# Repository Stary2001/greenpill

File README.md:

Greenpill
===
*Breadboard-able SAMD51 development board*

Inspired by the popular low-cost "Bluepill" and "Blackpill" STM32 boards, Greenpill aims to maintain some compatibility with those designs while adding features from the SAMD5x platform. Greenpill is designed to be used with [CircuitPython], although a SAMD51 port of Arduino could also be used.

## Features
 - SAMD51J20A-M microcontroller
   - Arm Cortex-M4 @ 120 MHz
   - 8 USB endpoints &ndash; enough for CDC & MSC (for CircuitPython), and some extras (eg. AUDIO)
 - Reversible USB Type-C connector supporting USB 2.0 data rates
 - On-board user LED and button
 - External 32.768 kHz crystal oscillator for RTC + clock source.
 - Up to 13 PWM-capable pins usable **simultaneously**
 - SPI flash footprint on underside - no pin conflicts with broken out pins (uses **SERCOM2**).

## Flashing CircuitPython
1. **TODO: add UF2 bootloader instructions**
2. [Build CircuitPython][BuildCPy] from [the fork][CPyFork]. Use the `atsamd` port and `BOARD=greenpill`.
3. Enter the UF2 bootloader by double-tapping the RESET button on Greenpill
4. You should now have a removable storage device called `CPYBOOT`. Copy `PATHTOUF2` to the root directory of this device. Once it has finished copying, `CPYBOOT` will disappear and `GREENPILL` will appear. You have now installed CircuitPython.

## Pin assignment
Pins are numbered **counter-clockwise** starting at the top-left pin (to the left of the USB-C connector).

| Greenpill Pin | GPIO name  | Available SERCOMs*               | Available PWM timers*                 | Comment                        |
|---------------|------------|----------------------------------|---------------------------------------|--------------------------------|
| User LED      | PB09       | -                                | TC4/WO[1]                             |                                |
| User Button   | PB06       | -                                | -                                     | Externally pulled up to 3v3    |
| VBat sense    | PB03       | -                                | -                                     | Connected to VBat via diode D3 |
| 1             | PA16       | SERCOM1/PAD[0]<br>SERCOM3/PAD[1] | TCC1/WO[0]<br>TCC0/WO[4]              |                                |
| 2             | PA17       | SERCOM1/PAD[1]<br>SERCOM3/PAD[0] | TC2/WO[1]<br>TCC1/WO[1]<br>TCC0/WO[5] |                                |
| 3             | PA18       | SERCOM1/PAD[2]<br>SERCOM3/PAD[2] | TCC1/WO[2]<br>TCC0/WO[6]              |                                |
| 4             | PA19       | SERCOM1/PAD[3]<br>SERCOM3/PAD[3] | TC3/WO[1]<br>TCC1/WO[3]<br>TCC0/WO[7] |                                |
| 5             | PB16       | SERCOM5/PAD[0]                   | TCC3/WO[0]<br>TCC0/WO[4]              |                                |
| 6             | PB01       | SERCOM5/PAD[3]                   | TC7/WO[1]                             |                                |
| 7             | PB00       | SERCOM5/PAD[2]                   | -                                     |                                |
| 8             | PA24       |                                  |                                       | USB D-                         |
| 9             | PA25       |                                  |                                       | USB D+                         |
| 10            | PA20       | SERCOM5/PAD[2]<br>SERCOM3/PAD[2] | TCC1/WO[4]<br>TCC0/WO[0] -            |                                |
| 11            | PB22       | SERCOM1/PAD[2]<br>SERCOM5/PAD[2] |                                       |                                |
| 12            | PB23       | SERCOM1/PAD[3]<br>SERCOM5/PAD[3] | TC7/WO[1]                             |                                |
| 13            | PA27       | -                                | -                                     |                                |
| 14            | PB31       | SERCOM5/PAD[0]                   | TC0/WO[1]<br>TCC4/WO[1]<br>TCC0/WO[7] |                                |
| 15            | PA22       | SERCOM3/PAD[0]<br>SERCOM5/PAD[1] | TCC1/WO[6]<br>TCC0/WO[2]              |                                |
| 16            | PB17       | SERCOM5/PAD[1]                   | TC6/WO[1]<br>TCC3/WO[1]<br>TCC0/WO[5] |                                |
| 17            | PB02       | SERCOM5/PAD[0]                   | TCC2/WO[2]                            |                                |
| 18            | **5V**     |                                  |                                       |                                |
| 19            | **Ground** |                                  |                                       |                                |
| 20            | **3.3V**   |                                  |                                       |                                |
| 21            | VBat       |                                  |                                       |                                |
| 22            | PB04       | -                                | -                                     |                                |
| 23            | PA03       | -                                | -                                     |                                |
| 24            | PB30       | SERCOM5/PAD[1]                   | TCC4/WO[0]<br>TCC0/WO[6]              |                                |
| 25            | ¬Reset     |                                  |                                       |                                |
| 26            | PA02       | -                                | -                                     |                                |
| 27            | PA08       | SERCOM4/PAD[0]                   | -                                     |                                |
| 28            | PA05       | SERCOM0/PAD[1]                   | TC0/WO[1]                             |                                |
| 29            | PA07       | SERCOM0/PAD[3]                   | TC1/WO[1]                             |                                |
| 30            | PA06       | SERCOM0/PAD[2]                   | -                                     |                                |
| 31            | PA04       | SERCOM0/PAD[0]                   | -                                     |                                |
| 32            | PA09       | SERCOM0/PAD[1]                   | TC0/WO[1]<br>TCC0/WO[1]<br>TCC1/WO[5] |                                |
| 33            | PA10       | SERCOM0/PAD[2]                   | TCC0/WO[2]<br>TCC1/WO[6]              |                                |
| 34            | PB10       | SERCOM4/PAD[2]                   | TCC0/WO[4]<br>TCC1/WO[0]              |                                |
| 35            | PB11       | SERCOM4/PAD[3]                   | TC5/WO[1]<br>TCC0/WO[5]<br>TCC1/WO[1] |                                |
| 36            | PB12       | SERCOM4/PAD[0]                   | TCC3/WO[0]<br>TCC0/WO[0]              |                                |
| 37            | PB13       | SERCOM4/PAD[1]                   | TC4/WO[1]<br>TCC3/WO[1]<br>TCC0/WO[1] |                                |
| 38            | **3.3V**   |                                  |                                       |                                |
| 39            | **Ground** |                                  |                                       |                                |
| 40            | **5V**     |                                  |                                       |                                |

\* SERCOM2 and all TC*n*/WO[0] have been removed from this table. SERCOM2 is used by the SPI flash, and TC*n*/WO[0] timers are not usable for PWM output by CircuitPython. For a full reference of pin capability, see Table 6-1 in the [SAM D5x datasheet][samd5xdata]

## License
The contents of this repository, which include the Greenpill hardware, documentation, and design files, are released under the **Solderpad 2.1 license**. The recommended firmware for GreenPill (CircuitPython) is NOT part of this repository. Both [Adafruit/CircuitPython][CircuitPython] and the [fork][CPyFork] that provides Greenpill compatibility are released under the **MIT License** 

[CircuitPython]: https://github.com/Adafruit/CircuitPython "Adafruit/CircuitPython on GitHub"
[CPyFork]: https://github.com/Stary2001/circuitpython/tree/greenpill "Branch 'greenpill' from Stary2001/CircuitPython on GitHub; forked from Adafruit"
[BuildCPy]: https://learn.adafruit.com/building-circuitpython?view=all "Building CircuitPython | Adafruit Learning System"
[samd5xdata]: https://ww1.microchip.com/downloads/en/DeviceDoc/SAM_D5xE5x_Family_Data_Sheet_DS60001507F.pdf "SAM D5x/E5x Family Data Sheet | Microchip (PDF)"

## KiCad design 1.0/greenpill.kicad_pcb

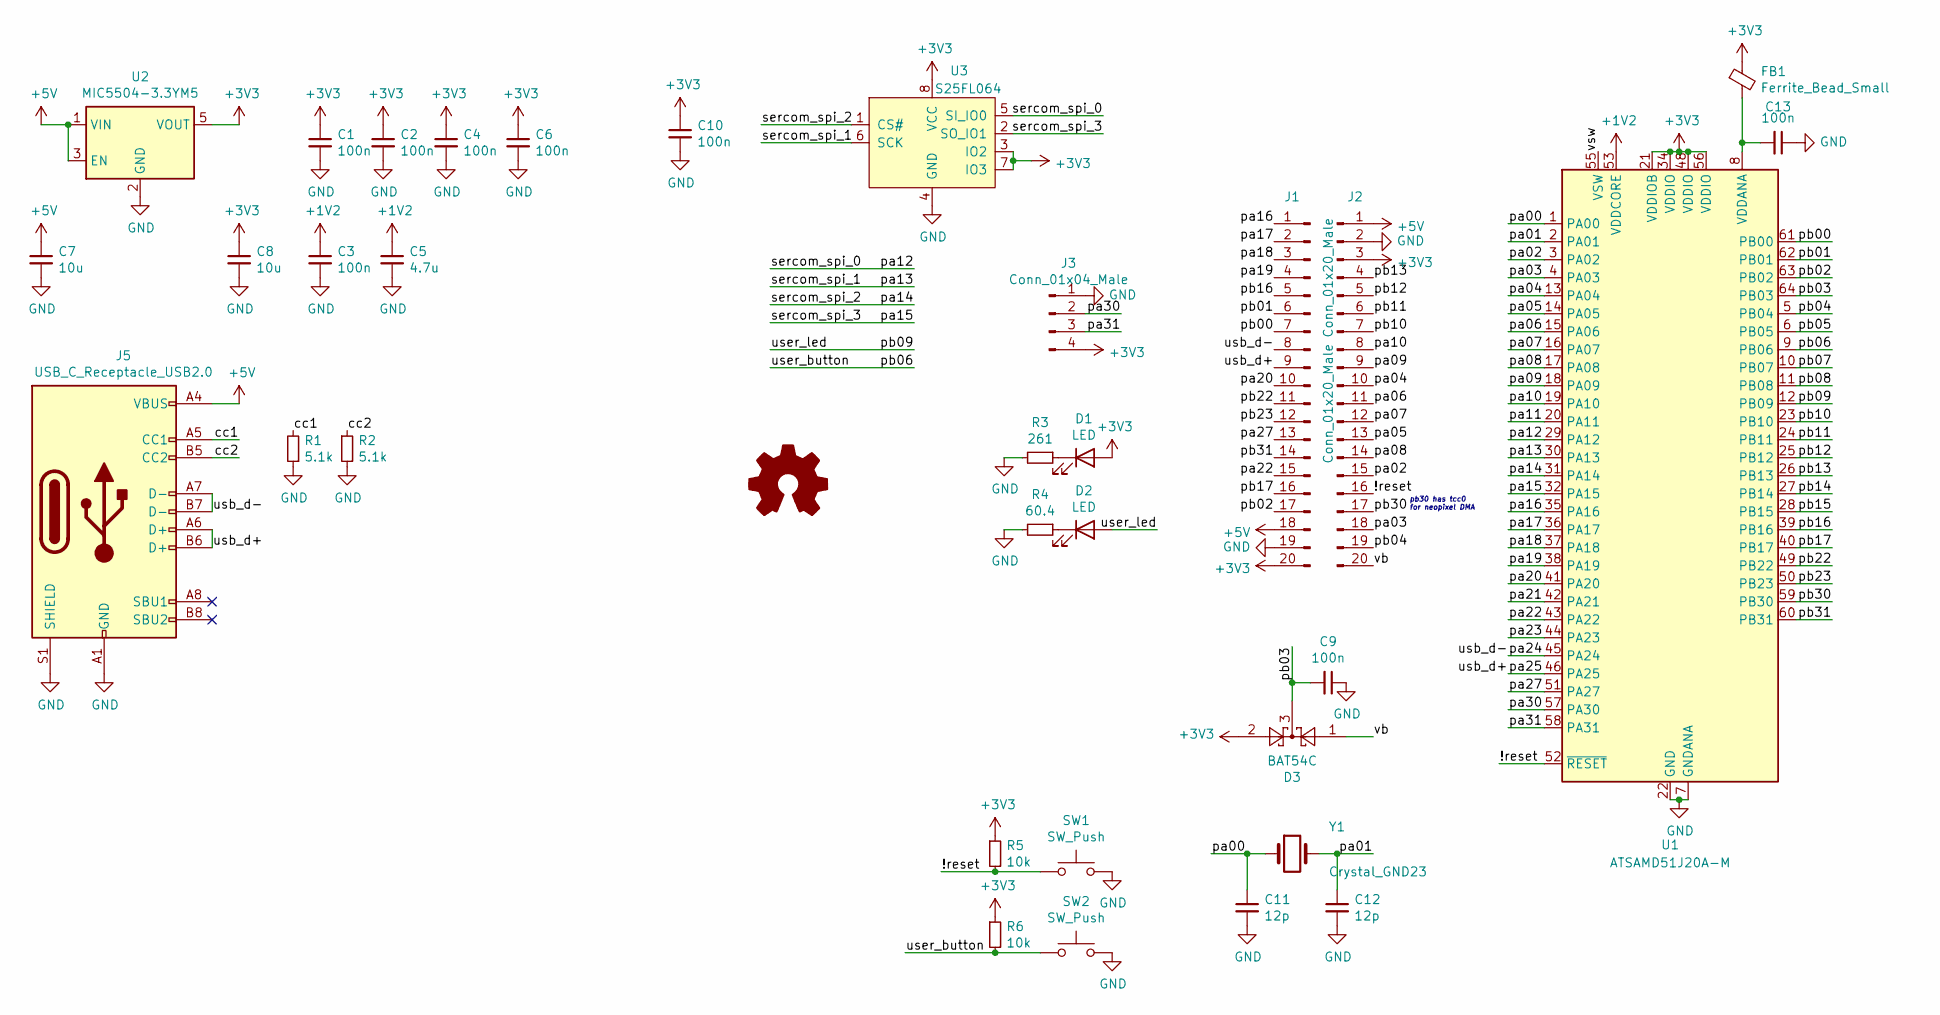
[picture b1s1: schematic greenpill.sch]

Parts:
C1, C2, C3, C4, C6, C9, C10: 100n; C_0402_1005Metric; MPN GRM155R61A104KA01J
C5: 4.7u; C_0603_1608Metric; MPN CL10A475KQ8NNNC
C7, C8: 10u; C_0603_1608Metric; MPN GRM188R61A106KE69J
C11, C12: 12p; C_0603_1608Metric; MPN C0603C120J5GACTU
C13: 100n; C_0402_1005Metric
D1: LED; LED_0603_1608Metric; MPN 150060RS75000
D2: LED; LED_0603_1608Metric; MPN 150060BS75000
D3: BAT54C; SOT-23; MPN BAT54C,215
FB1: Ferrite_Bead_Small; R_0603_1608Metric_Pad1.05x0.95mm_HandSolder
J1, J2: Conn_01x20_Male; PinHeader_1x20_P2.54mm_Vertical
J3: Conn_01x04_Male; PinHeader_1x04_P2.54mm_Horizontal
J5: USB_C_Receptacle_USB2.0; USB_C_Receptacle_XKB_U262-16XN-4BVC11; MPN lmao aliexpress
LOGO1: Logo_Open_Hardware_Small; OSHW-Symbol_4x4.5mm_SilkScreen
R1, R2: 5.1k; R_0603_1608Metric; MPN RC0603FR-075K1L
R3: 261; R_0603_1608Metric; MPN P261HCT-ND
R4: 60.4; R_0603_1608Metric; MPN RC0603FR-0760R4L
R5, R6: 10k; R_0603_1608Metric; MPN RC0603FR-0710KL
SW1, SW2: SW_Push; PTS636; MPN PTS815 SJM 250 SMTR LFS
U1: ATSAMD51J20A-M; QFN-64-1EP_9x9mm_P0.5mm_EP4.7x4.7mm; MPN ATSAMD51J20A-MU
U2: MIC5504-3.3YM5; SOT-23-5; MPN MIC5504-3.3YM5-TR
U3: S25FL064; SOIC-8_5.23x5.23mm_P1.27mm; MPN S25FL064LABMFN010
Y1: Crystal_GND23; Crystal_SMD_3215-2Pin_3.2x1.5mm; MPN FC-135 32.7680KA-A5

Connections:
+1V2: C3.1, C5.1, U1.53 (VDDCORE)
+3V3: C1.1, C2.1, C4.1, C6.1, C8.1, C10.1, D1.2 (A), D3.2, FB1.1, J1.20, J2.3, J3.4, R5.1, R6.1, U1.21 (VDDIOB), U1.34 (VDDIO), U1.48 (VDDIO), U1.56 (VDDIO), U2.5 (VOUT), U3.3 (IO2), U3.7 (IO3), U3.8 (VCC)
+5V: C7.1, J1.18, J2.1, J5.A4 (VBUS), J5.A9 (VBUS), J5.B4 (VBUS), J5.B9 (VBUS), U2.1 (VIN), U2.3 (EN)
/!reset: J2.16, R5.2, SW1.1, U1.52 (~RESET)
/cc1: J5.A5 (CC1), R1.2
/cc2: J5.B5 (CC2), R2.1
/pa00: C11.1, U1.1 (PA00), Y1.1
/pa01: C12.1, U1.2 (PA01), Y1.2
/pa02: J2.15, U1.3 (PA02)
/pa03: J2.18, U1.4 (PA03)
/pa04: J2.10, U1.13 (PA04)
/pa05: J2.13, U1.14 (PA05)
/pa06: J2.11, U1.15 (PA06)
/pa07: J2.12, U1.16 (PA07)
/pa08: J2.14, U1.17 (PA08)
/pa09: J2.9, U1.18 (PA09)
/pa10: J2.8, U1.19 (PA10)
/pa11: U1.20 (PA11)
/pa12: U1.29 (PA12), U3.5 (SI_IO0)
/pa13: U1.30 (PA13), U3.6 (SCK)
/pa14: U1.31 (PA14), U3.1 (CS#)
/pa15: U1.32 (PA15), U3.2 (SO_IO1)
/pa16: J1.1, U1.35 (PA16)
/pa17: J1.2, U1.36 (PA17)
/pa18: J1.3, U1.37 (PA18)
/pa19: J1.4, U1.38 (PA19)
/pa20: J1.10, U1.41 (PA20)
/pa21: U1.42 (PA21)
/pa22: J1.15, U1.43 (PA22)
/pa23: U1.44 (PA23)
/pa24: J1.8, J5.A7 (D-), J5.B7 (D-), U1.45 (PA24)
/pa25: J1.9, J5.A6 (D+), J5.B6 (D+), U1.46 (PA25)
/pa27: J1.13, U1.51 (PA27)
/pa30: J3.2, U1.57 (PA30)
/pa31: J3.3, U1.58 (PA31)
/pb00: J1.7, U1.61 (PB00)
/pb01: J1.6, U1.62 (PB01)
/pb02: J1.17, U1.63 (PB02)
/pb03: C9.2, D3.3, U1.64 (PB03)
/pb04: J2.19, U1.5 (PB04)
/pb05: U1.6 (PB05)
/pb06: R6.2, SW2.1, U1.9 (PB06)
/pb07: U1.10 (PB07)
/pb08: U1.11 (PB08)
/pb09: D2.2 (A), U1.12 (PB09)
/pb10: J2.7, U1.23 (PB10)
/pb11: J2.6, U1.24 (PB11)
/pb12: J2.5, U1.25 (PB12)
/pb13: J2.4, U1.26 (PB13)
/pb14: U1.27 (PB14)
/pb15: U1.28 (PB15)
/pb16: J1.5, U1.39 (PB16)
/pb17: J1.16, U1.40 (PB17)
/pb22: J1.11, U1.49 (PB22)
/pb23: J1.12, U1.50 (PB23)
/pb30: J2.17, U1.59 (PB30)
/pb31: J1.14, U1.60 (PB31)
/vb: D3.1, J2.20
/vsw: U1.55 (VSW)
GND: C1.2, C2.2, C3.2, C4.2, C5.2, C6.2, C7.2, C8.2, C9.1, C10.2, C11.2, C12.2, C13.1, J1.19, J2.2, J3.1, J5.A1 (GND), J5.A12 (GND), J5.B1 (GND), J5.B12 (GND), J5.S1 (SHIELD), R1.1, R2.2, R3.2, R4.2, SW1.2, SW2.2, U1.7 (GNDANA), U1.22 (GND), U1.33 (GND), U1.47 (GND), U1.54 (GND), U1.65 (GND), U2.2 (GND), U3.4 (GND)
unnamed: C13.2, FB1.2, U1.8 (VDDANA)
unnamed: D1.1 (K), R3.1
unnamed: D2.1 (K), R4.1

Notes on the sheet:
pb30 has tcc0 for neopixel DMA

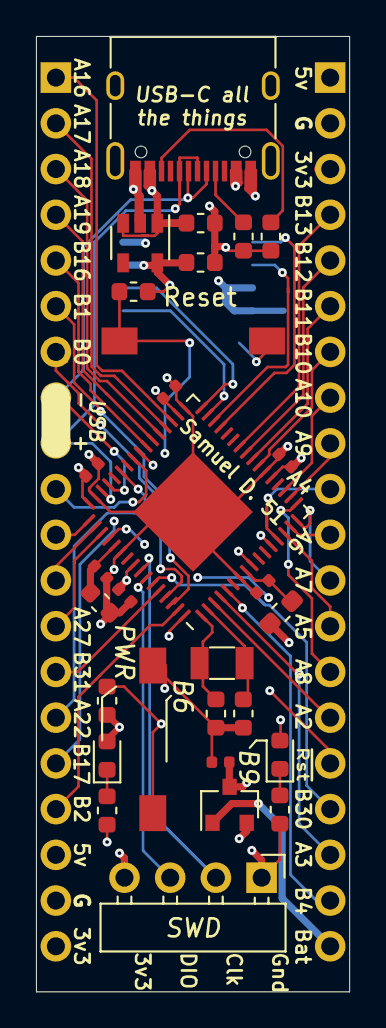
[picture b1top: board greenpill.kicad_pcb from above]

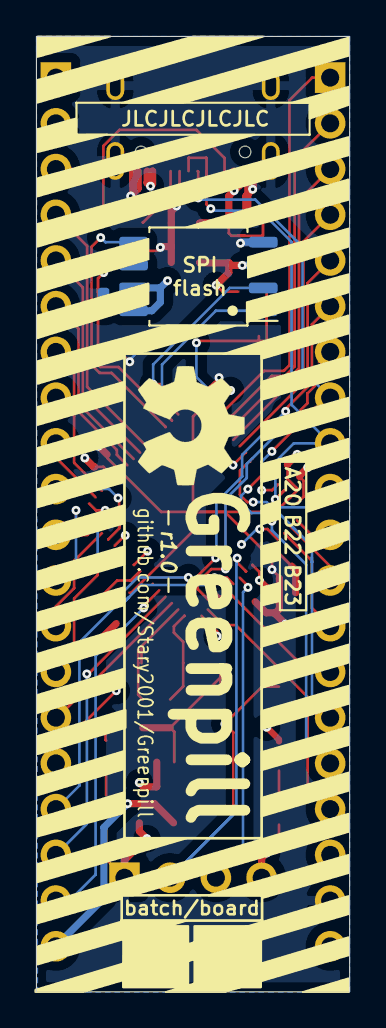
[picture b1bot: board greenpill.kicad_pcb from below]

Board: 4 copper layers, 17.4 x 53.1 mm, 33 parts (2 on the bottom side), 54 nets.

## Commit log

2020-06-29 Trimmed board, added pinout silkscreen
2020-06-29 PINOUT CHANGE, rerouted and updated silk.s
    Swapped left pins 13 and 16 (formerly A21 & A27 respectively) so PWM output on A21 can be used for Textier LED4:G. A27 now on pin L13 is used for key matrix scanning and so doesn't require PWM
    Rerouted only affected traces
    Swapped silkscreen labels
2020-06-29 a bit of tweaking
2020-07-05 Switched to QFN-64 package, reassigned pins. Trimmed Edge.Cuts
    Still TODO:
    - Redo silkscreen
    - Move passives near MCU to optimal position (1v2 caps especially)
2020-07-06 Routed trivial IOs
2020-07-11 yeet
2020-07-11 Updated silkscreen
2020-07-11 poke layout a bit
2020-07-11 Added 3D models
2020-07-11 Added * f u n k y * back silkscreen, some front silkscreen tweaks
2020-07-11 swapped button and led to non broken out pins
2020-07-24 add mpns
2020-07-25 revert meme
2020-08-31 1.0??
2020-09-03 change pinout to hopefully have full timer coverage
2020-09-13 Added github actions for KiPlot
2020-09-13 Whoops moved config.kiplot.yaml to the right dir
2020-09-13 Moved `ls` up
2020-09-13 Changed to consistent lower case
2020-09-13 Change to only using the first page
2020-09-13 Add empty docs/ folder
2020-09-13 Add commit step to CI
2020-09-13 Updated auto-generated files in docs/
2020-09-13 Added index.html to redirect to github
2020-09-13 Only run Github Actions when KiCAD files change
2020-09-13 Started documentation; some stuff still TODO
2020-09-13 Updated index.md
    - User LED doesn't have PWM
    - Added SPI flash note
    - Added building CPy details
    - Fixed link to forked CPy
2020-09-13 Add GitHub Actions CI for generating schematics (closes #8) (#11)
    Seems good enough
    * Added github actions for KiPlot
    * Whoops moved config.kiplot.yaml to the right dir
    * Moved `ls` up
    * Changed to consistent lower case
    * Change to only using the first page
2020-09-13 Added solderpad license (closes #5)
2020-09-13 Added note about SPI flash SERCOM 2
2020-09-13 Moved User LED from PB08 to PB09
    - Updated schematic
    - Rerouted trace
    - Updated silkscreen
2020-09-13 Rename index.md to README.md
    Whoops I forgot what the default file for a repository should be
2020-09-16 Fix silkscreen for new pinout, add PTS636 3D model.
2020-09-16 move silkscreen around on the bottom, add gear logo, adjust copper text
2020-09-17 attempt to add image
2020-09-17 oops, remove 2nd schematic
2020-09-19 shift around basically all the silkscreen on the back
2020-09-27 Moved board/batch number boxes on B.SilkS
2020-09-28 Added r1.0 text
